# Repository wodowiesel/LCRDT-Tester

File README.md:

# LCRDT-Tester

The Tester is a tool for identification of the electronic components and its values based on Arduino Nano v3 with internal reference incl. pcb schematics & code.

Compatibility list:

- Inductors
- Capacitors
- Resistors
- Diodes
- Transistors

- Vloss
- ESR
- Type (PNP/NPN/FET/MOS)
- hFE B

## DISCLAIMERS

**This is still "work-in-progress (WIP)" so I do NOT take any kind of responsibility for damages/data losses!**

**You can use this at your own risk without guarantees and put device on non conductive surface or enclosure!**

If you like the new design yo are free to share it!

Have fun :)

## HARDWARE

- 1x Arduino Nano v3 (or Uno for old versions) + USB-Cable
- 1x Custom PCB for Arduino Nano v3 by WodoWiesel
- 3x 10 kOhm Resistors
- 3x 330 Ohm Resistors
- 1x 100 nF capacitor (or without, just bridge it)
- 1x 4-pin display for +3.3V (0.96" OLED)
- 2x Push-Button (reset & start)
- 1x 3-Pin Male Pin Header (for component testing)
- 1x 4-Pin Male Pin Header (for display)

- 1x Soldering iron
- Solder + flux + IPA

## SOFTWARE

Download my adapted [code](/code-aduino/LCRDT-Tester-WodoWiesel.ino) and configure your setup and load it via Arduino IDE.

## HOW TO USE

1. configure code adapted to your setup regarding used parts and display type

2. upload code to your arduino

3. solder the new pcb

4. put component of choice in the testing headers and read values

## CREDITS

:copyright: 10/10/2023 WodoWiesel

Github (https://github.com/wodowiesel/)

Twitch (https://www.twitch.com/wodowiesel/)

Instagram (https://www.instagram.com/wodowiesel/)

YT (https://www.youtube.com/@wodowiesel/)

E-Mail (wodowiesel@quantentunnel.de)

The new design was checked by the electrical engineer theBrutzler

(https://github.com/theBrutzler/ & https://www.twitch.com/theBrutzler/)

The new optimized PCB was designed with free KiCAD software (https://www.kicad.org/)

:heavy_exclamation_mark: The PCB should be produced at a manufacturer

(like PCBWay or similar) with the RoHS lead-free option for environmental protection.

Originals:

Proekty (https://arduino.ru/forum/proekty/transistor-tester-arduino/)

Vlad (https://github.com/vlad-gheorghe/ardutester/)

Code: Karl-Heinz Kubbeler (version 1.08k, 2013 / 1.10, 2014)

engl. Journal [PDF](/docs/ttester_eng108k.pdf)

## LICENSES

- Hardware

CERN Open Hardware License Version 2 - Weakly Reciprocal

Short identifier CERN-OHL-W-2.0

[LICENSE Source](https://spdx.org/licenses/CERN-OHL-W-2.0.html)

- Software

This work is licensed under a Creative Commons Attribution-NonCommercial 3.0 Unported License.

[CCANC](http://creativecommons.org/licenses/by-nc/3.0/)

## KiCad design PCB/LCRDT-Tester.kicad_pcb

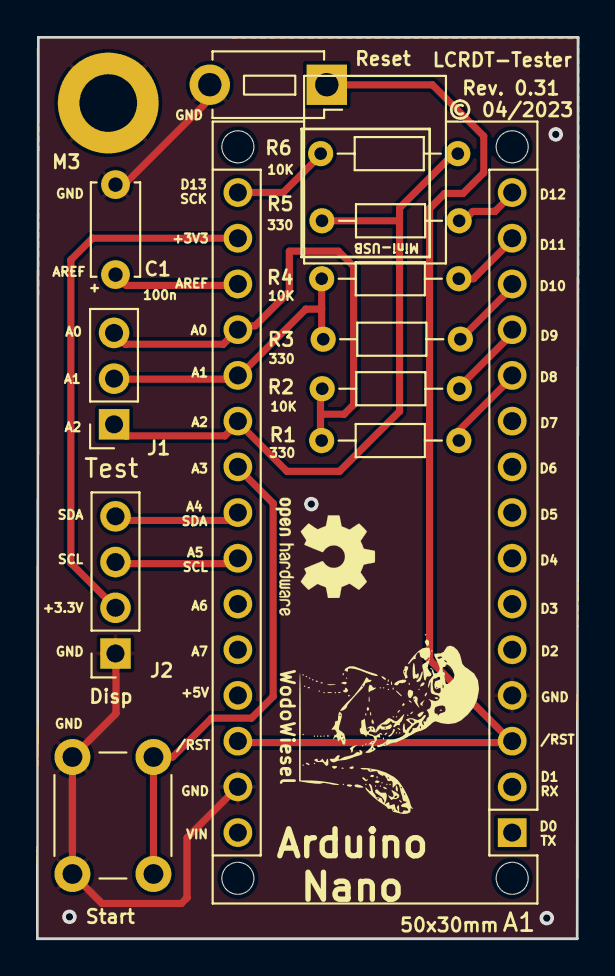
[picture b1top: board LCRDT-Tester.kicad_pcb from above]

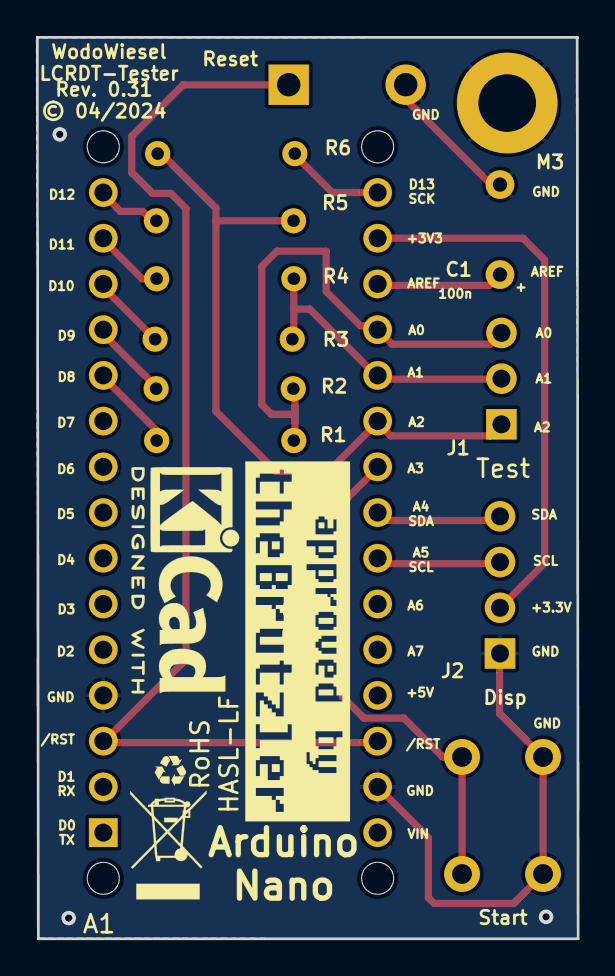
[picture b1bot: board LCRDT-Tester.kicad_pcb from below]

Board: 2 copper layers, 30.0 x 50.1 mm, 18 parts (4 on the bottom side), 16 nets.

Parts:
A1: Arduino_Nano_v3.x; Arduino_Nano_WithMountingHoles
C1: 100n; C_Disc_D5.0mm_W2.5mm_P5.00mm
G3*: LOGO; recycling-symbol-kicad
G6**: LOGO; approved_theBrutzler
G21: LOGO; wiesel-kicad-back-white
J1: Test; PinSocket_1x03_P2.54mm_Vertical
J2: Disp; PinSocket_1x04_P2.54mm_Vertical
R1, R3, R5: 330; R_Axial_DIN0204_L3.6mm_D1.6mm_P7.62mm_Horizontal
R2, R4, R6: 10K; R_Axial_DIN0204_L3.6mm_D1.6mm_P7.62mm_Horizontal
REF7**: WEEE-Logo_4.2x6mm_SilkScreen
REF8**: KiCad-Logo2_5mm_SilkScreen
REF9**: MountingHole_3.2mm_M3_DIN965_Pad
Reset: SW_Push; SW_PUSH_1P1T_6x3.5mm_H4.3_APEM_MJTP1243
Start: SW_Push; SW_PUSH_6mm_H4.3mm

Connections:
GND: A1.4 (GND), A1.29 (GND), C1.2, J2.1, REF9**.1, Reset.2, Start.2
unnamed: A1.17 (3V3), J2.2
unnamed: A1.19 (A0), J1.3, R1.1, R2.2
unnamed: A1.20 (A1), J1.2, R3.1, R4.2
unnamed: A1.21 (A2), J1.1, R5.1, R6.2
unnamed: A1.22 (A3), Start.1
unnamed: A1.23 (A4), J2.4
unnamed: A1.24 (A5), J2.3
unnamed: A1.18 (AREF), C1.1
unnamed: A1.11 (D8), R1.2
unnamed: A1.12 (D9), R2.1
unnamed: A1.13 (D10), R3.2
unnamed: A1.14 (D11), R4.1
unnamed: A1.15 (D12), R5.2
unnamed: A1.16 (D13), R6.1
unnamed: A1.3 (~RESET), A1.28 (~RESET), Reset.1

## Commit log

2023-09-16 init pcb/schemetics/docs/code
    init pcb/schemetics/docs/code
2023-09-16 fix typos
2023-10-09 -added m3 mounting hole -added start button -more compact design -added logos -added 3d arduino shapes wrl -updated docs & readme -updated code
2023-10-09 schematics
2023-10-11 -adapt code to custom resistor val -activate autoscale -changed rst pin nr -deactivate rus charset lcd (optional) using english
2023-10-14 upload gerber, drill and different export files
2023-10-14 relocate
2023-10-21 fix typo
2023-10-21 better summary
2023-12-16 optimize code 0.96" oled display
2024-04-05 cleanups+Mountingholes

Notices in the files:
PCB/LCRDT-Tester.kicad_pcb:
© 04/2024
© 04/2023
